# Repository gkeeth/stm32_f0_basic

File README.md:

# stm32_f0_basic
Small, bare-bones STM32F0 board

Designed for STM32F031K6. Most likely works for other MCUs as well.

Created as a test before making a bigger board. If it's useful on its own, even better.

This work is licensed under a [Creative Commons Attribution-ShareAlike 4.0
International License][cc-by-sa].

[![CC BY-SA 4.0][cc-by-sa-image]][cc-by-sa]

[cc-by-sa]: http://creativecommons.org/licenses/by-sa/4.0/
[cc-by-sa-image]: https://licensebuttons.net/l/by-sa/4.0/88x31.png

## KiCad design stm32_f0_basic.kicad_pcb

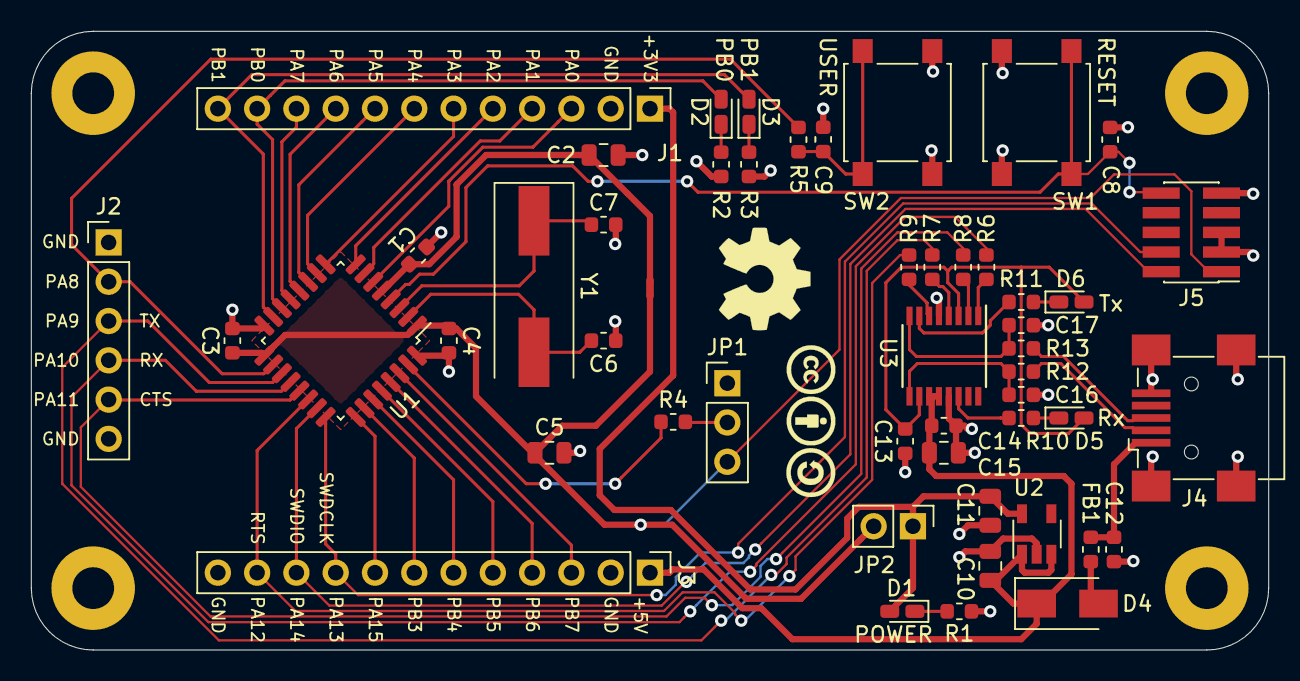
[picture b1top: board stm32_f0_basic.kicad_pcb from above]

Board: 2 copper layers, 80.0 x 40.0 mm, 58 parts (1 on the bottom side), 52 nets.

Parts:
C1, C12: 10n; C_0603_1608Metric
C2, C10, C11: 1u; C_0805_2012Metric
C3, C4, C8, C9, C13, C14: 100n; C_0603_1608Metric
C5, C15: 4.7u; C_0805_2012Metric
C6, C7: 27p; C_0603_1608Metric
C16, C17: 47pF; C_0603_1608Metric
D1: red; LED_0603_1608Metric_Castellated
D2: green; LED_0603_1608Metric_Castellated
D3: blue; LED_0603_1608Metric_Castellated
D4: B140-E3; D_SMA
D5: RX (green); LED_0603_1608Metric_Castellated
D6: TX (red); LED_0603_1608Metric_Castellated
FB1: Ferrite_Bead; L_0603_1608Metric
H1, H2, H3, H4: MountingHole_Pad; MountingHole_2.7mm_M2.5_Pad
J1, J3: Conn_01x12_Male; PinHeader_1x12_P2.54mm_Vertical
J2: Conn_01x06_Male; PinHeader_1x06_P2.54mm_Vertical
J4: USB_B_Mini; USB_Mini-B_Wuerth_65100516121_Horizontal
J5: Conn_ARM_JTAG_SWD_10; PinHeader_2x05_P1.27mm_Vertical_SMD
JP1: Jumper_3_Bridged12; PinHeader_1x03_P2.54mm_Vertical
JP2: Jumper_2_Bridged; PinHeader_1x02_P2.54mm_Vertical
LOGO1: Logo_Open_Hardware_Small; OSHW-Symbol_6.7x6mm_SilkScreen
LOGO2: CC-BY-SA_0.33in; CC-BY-SA_SilkScreenTop_Small
LOGO3: Logo_MadeWithKiCad; KiCad-Logo2_5mm_SilkScreen
NT1: Net-Tie_2; NetTie-2_SMD_Pad0.5mm
R1: 1k; R_0603_1608Metric
R2, R10, R11: 330; R_0603_1608Metric
R3: 660; R_0603_1608Metric
R4: 10k; R_0603_1608Metric
R5, R6, R7, R8, R9: 0; R_0603_1608Metric
R12, R13: 27; R_0603_1608Metric
SW1, SW2: B3S-1000P; SW_SPST_B3S-1000
U1: STM32F031K6Tx; LQFP-32_7x7mm_P0.8mm
U2: ADP121-AUJZ33R7; TSOT-23-5
U3: FT230XS; SSOP-16_3.9x4.9mm_P0.635mm
Y1: 8MHz; Crystal_SMD_HC49-SD

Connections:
+3V3: C11.1, D1.2, J1.1, JP2.1, U2.5
+5V: C10.1, C14.2, C15.1, D4.1, J3.1, U2.1, U2.3, U3.11, U3.12
/stm32f0/BOOT0: R4.1, U1.31
/stm32f0/NRST: C8.1, J5.10, SW1.2, U1.4
/stm32f0/PA0: J1.3, U1.6
/stm32f0/PA1: J1.4, U1.7
/stm32f0/PA2: J1.5, U1.8
/stm32f0/PA3: J1.6, U1.9
/stm32f0/PA4: J1.7, U1.10
/stm32f0/PA5: J1.8, U1.11
/stm32f0/PA6: J1.9, U1.12
/stm32f0/PA7: J1.10, U1.13
/stm32f0/PA8: J2.2, R5.2, U1.18
/stm32f0/PA9_USART1_TX: J2.3, R7.2, U1.19
/stm32f0/PA10_USART1_RX: J2.4, R6.2, U1.20
/stm32f0/PA11_USART1_CTS: J2.5, R8.2, U1.21
/stm32f0/PA12_USART1_RTS: J3.11, R9.2, U1.22
/stm32f0/PA13_SWDIO: J3.10, J5.2, U1.23
/stm32f0/PA14_SWDCLK: J3.9, J5.4, U1.24
/stm32f0/PA15: J3.8, U1.25
/stm32f0/PB0: D2.2, J1.11, U1.14
/stm32f0/PB1: D3.2, J1.12, U1.15
/stm32f0/PB3: J3.7, U1.26
/stm32f0/PB4: J3.6, U1.27
/stm32f0/PB5: J3.5, U1.28
/stm32f0/PB6: J3.4, U1.29
/stm32f0/PB7: J3.3, U1.30
/usb_uart/UART_CTS: R9.1, U3.6
/usb_uart/UART_RTS: R8.1, U3.2
/usb_uart/UART_RXD: R7.1, U3.4
/usb_uart/UART_TXD: R6.1, U3.1
/usb_uart/USBUART+: C17.1, R13.1, U3.8
/usb_uart/USBUART-: C16.1, R12.1, U3.9
/usb_uart/USB_D+: J4.3, R13.2
/usb_uart/USB_D-: J4.2, R12.2
GND: C1.2, C2.2, C3.2, C4.2, C5.2, C6.2, C7.2, C8.2, C9.2, C10.2, C11.2, C12.1, C13.1, C14.1, C15.2, C16.2, C17.2, H1.1, H2.1, H3.1, H4.1, J1.2, J2.1, J2.6, J3.2, J3.12, J4.5, J4.6, J5.3, J5.5, J5.9, JP1.1, R1.1, R2.1, R3.1, SW1.1, SW2.1, U1.16, U1.32, U2.2, U3.5, U3.13
unnamed: C6.1, U1.2, Y1.2
unnamed: C7.1, U1.3, Y1.1
unnamed: C9.1, R5.1, SW2.2
unnamed: C12.2, FB1.2, J4.1
unnamed: C13.2, D5.2, D6.2, U3.3, U3.10
unnamed: D1.1, R1.2
unnamed: D2.1, R2.2
unnamed: D3.1, R3.2
unnamed: D4.2, FB1.1
unnamed: D5.1, R10.2
unnamed: D6.1, R11.2
unnamed: JP1.2, R4.2
unnamed: R10.1, U3.14
unnamed: R11.1, U3.7
VDD: C3.1, C4.1, C5.1, J5.1, JP1.3, JP2.2, NT1.1, U1.1, U1.17
VDDA: C1.1, C2.1, NT1.2, U1.5

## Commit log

2019-10-05 add CC-BY-SA 4.0 license
2019-10-05 add reference PDFs from ST to gitignore
2019-10-05 add possible STM32 parts to notes
2019-10-07 add initial schematic
2019-10-07 update gitignore
2019-10-07 update FTDI decoupling, add ferrite to VBUS, add mounting holes
2019-10-14 add fp-info-cache to gitignore
2019-10-14 complete initial layout
    * components placed
    * all nets routed
    * switches, LEDs, connectors labeled
    * TODO: route USB DM/DP as a diff pair?
    * TODO: add 3D models for USB connector, pushbutton switches
2019-10-17 rearrange headers and update silk labels (in progress)
2019-10-17 Update USB schematic, redo lots of routing
    * add series resistors and shunt capacitors to usb diff pair
    * place usb-uart IC optimally for connecting to usb connector
    * move bypass caps and resistors attached to usb-uart
    * move user & reset buttons next to each other
    * move user LEDs close to buttons
    * move bottom connector
2019-10-17 Route USB traces
    * rename USB traces in schematic so they can be routed as a differential
    pair
    * route USB traces
    * note: USB traces are routed as a differential pair, but not as a
    transmission line of the correct 90R differential impedance, because
    it's not feasible on a 2-layer, 1.6mm board (traces would be huge).
2019-10-19 adjust traces and update TODO (3D models done)
2019-10-21 add Creative Commons/OSHW/Kicad/project info silkscreen
2019-12-14 minor planner updates
2019-12-14 adjust ground plane, add pin silk reference
2019-12-14 generate gerbers for r0 production
2019-12-14 add board images to README
2019-12-22 add bom info
2019-12-24 add basic blink example source code
2019-12-24 update blinking to be systick-based
2019-12-24 add button functionality to blink example
2019-12-26 Add several features to blink
    - added UART functionality:
    - echo any received bytes back
    - transmit blink delay whenever button is pressed (NOTE: continues
    to transmit as long as button is pressed; algorithm needs to change)
    - GPIOs PA0-2 now are asserted to indicate mode
2019-12-26 improve algorithm so blink speed changes only once per button press
2019-12-26 clean up blink.c
2019-12-26 combine GPIO setup calls for identical pins
2019-12-26 clean up clock setup; use external crystal
2019-12-26 add debug rule to makefile, and a gdb init script
2020-01-10 add STM32 part number to readme
2020-01-10 don't ignore cache and rescue libs
